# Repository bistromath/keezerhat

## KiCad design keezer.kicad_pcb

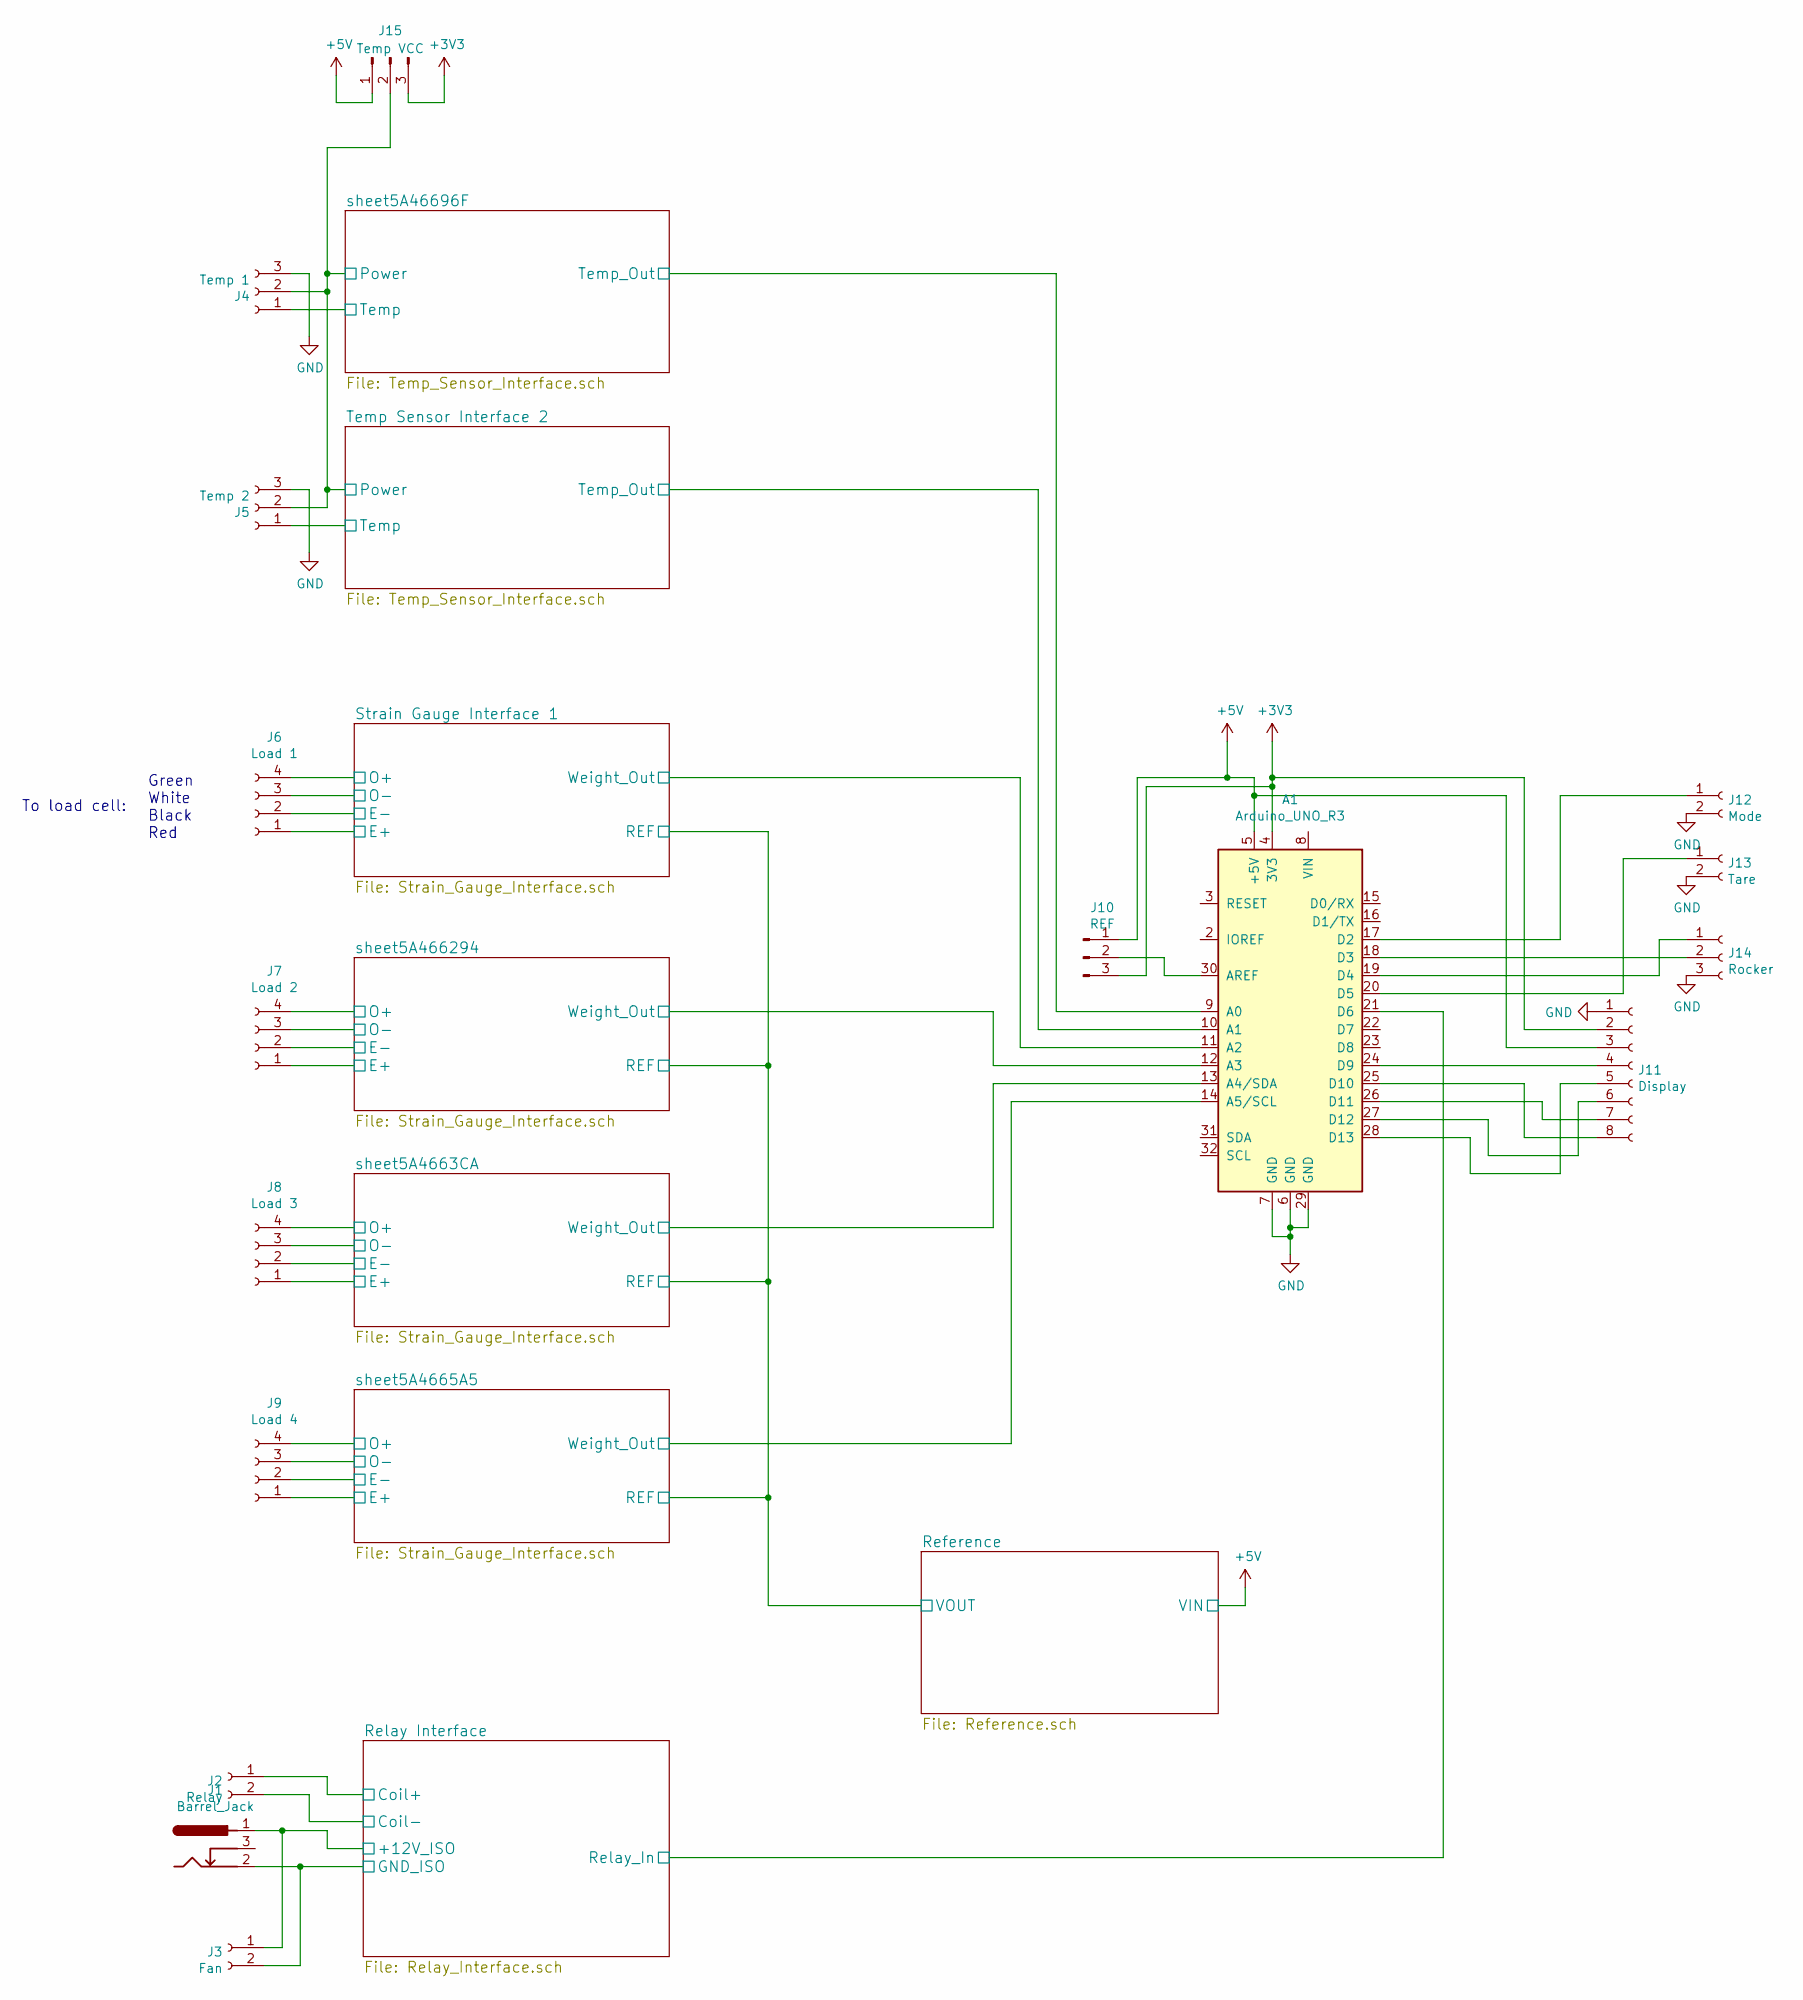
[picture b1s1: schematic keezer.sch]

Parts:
A1: Arduino_UNO_R3
J1: Barrel_Jack; Barrel_Jack_CUI_PJ-102AH
J2: Relay; Molex_NanoFit_1x02x2.50mm_Straight
J3: Fan; Molex_NanoFit_1x02x2.50mm_Straight
J4: Temp 1; Molex_NanoFit_1x03x2.50mm_Straight
J5: Temp 2; Molex_NanoFit_1x03x2.50mm_Straight
J6: Load 1; Molex_NanoFit_2x02x2.50mm_Straight
J7: Load 2; Molex_NanoFit_2x02x2.50mm_Straight
J8: Load 3; Molex_NanoFit_2x02x2.50mm_Straight
J9: Load 4; Molex_NanoFit_2x02x2.50mm_Straight
J10: REF; Pin_Header_Straight_1x03_Pitch2.54mm
J11: Display; Molex_NanoFit_2x04x2.50mm_Straight
J12: Mode; Molex_NanoFit_1x02x2.50mm_Straight
J13: Tare; Molex_NanoFit_1x02x2.50mm_Straight
J14: Rocker; Molex_NanoFit_1x03x2.50mm_Straight
J15: Temp VCC; Pin_Header_Straight_1x03_Pitch2.54mm

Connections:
+3V3: A1.4 (3V3), J10.3, J11.2, J15.3
+5V: A1.5 (+5V), J6.1, J7.1, J8.1, J9.1, J10.1, J11.3, J15.1; also elsewhere on the board
/Relay Interface/+12V_ISO: J1.1, J3.1; also elsewhere on the board
/Relay Interface/Coil+: J2.1; also elsewhere on the board
/Relay Interface/Coil-: J1.2, J2.2, J3.2; also elsewhere on the board
/Relay Interface/Relay_In: A1.21 (D6); also elsewhere on the board
/Strain Gauge Interface 1/O+: J6.4; also elsewhere on the board
/Strain Gauge Interface 1/O-: J6.3; also elsewhere on the board
/Strain Gauge Interface 1/Weight_Out: A1.11 (A2); also elsewhere on the board
/Temp Sensor Interface 2/Power: J4.2, J5.2, J15.2; also elsewhere on the board
/Temp Sensor Interface 2/Temp: J5.1; also elsewhere on the board
/Temp Sensor Interface 2/Temp_Out: A1.10 (A1); also elsewhere on the board
/sheet5A4663CA/O+: J8.4; also elsewhere on the board
/sheet5A4663CA/O-: J8.3; also elsewhere on the board
/sheet5A4663CA/Weight_Out: A1.13 (A4/SDA); also elsewhere on the board
/sheet5A4665A5/O+: J9.4; also elsewhere on the board
/sheet5A4665A5/O-: J9.3; also elsewhere on the board
/sheet5A4665A5/Weight_Out: A1.14 (A5/SCL); also elsewhere on the board
/sheet5A46696F/Temp: J4.1; also elsewhere on the board
/sheet5A46696F/Temp_Out: A1.9 (A0); also elsewhere on the board
/sheet5A466294/O+: J7.4; also elsewhere on the board
/sheet5A466294/O-: J7.3; also elsewhere on the board
/sheet5A466294/Weight_Out: A1.12 (A3); also elsewhere on the board
GND: A1.6 (GND), A1.7 (GND), A1.29 (GND), J4.3, J5.3, J6.2, J7.2, J8.2, J9.2, J11.1, J12.2, J13.2, J14.3; also elsewhere on the board
unnamed: A1.17 (D2), J12.1
unnamed: A1.18 (D3), J14.2
unnamed: A1.19 (D4), J14.1
unnamed: A1.20 (D5), J13.1
unnamed: A1.24 (D9), J11.4
unnamed: A1.25 (D10), J11.8
unnamed: A1.26 (D11), J11.7
unnamed: A1.27 (D12), J11.6
unnamed: A1.28 (D13), J11.5
unnamed: A1.30 (AREF), J10.2

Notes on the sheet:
Green White Black Red
To load cell:

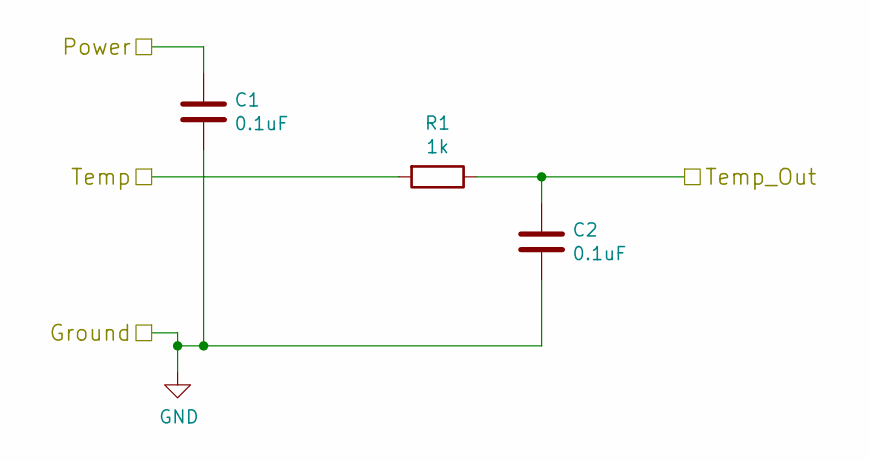
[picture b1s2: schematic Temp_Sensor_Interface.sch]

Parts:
C1, C2: 0.1uF; C_0805_HandSoldering
R1: 1k; R_0805_HandSoldering

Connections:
/Temp Sensor Interface 2/Power: C1.1; also elsewhere on the board
/Temp Sensor Interface 2/Temp: R1.2; also elsewhere on the board
/Temp Sensor Interface 2/Temp_Out: C2.1, R1.1; also elsewhere on the board
GND: C1.2, C2.2; also elsewhere on the board

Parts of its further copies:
C3, C4: 0.1uF; C_0805_HandSoldering
R4: 1k; R_0805_HandSoldering

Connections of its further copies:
/Temp Sensor Interface 2/Power: C3.1; also elsewhere on the board
/sheet5A46696F/Temp: R4.2; also elsewhere on the board
/sheet5A46696F/Temp_Out: C4.1, R4.1; also elsewhere on the board
GND: C3.2, C4.2; also elsewhere on the board

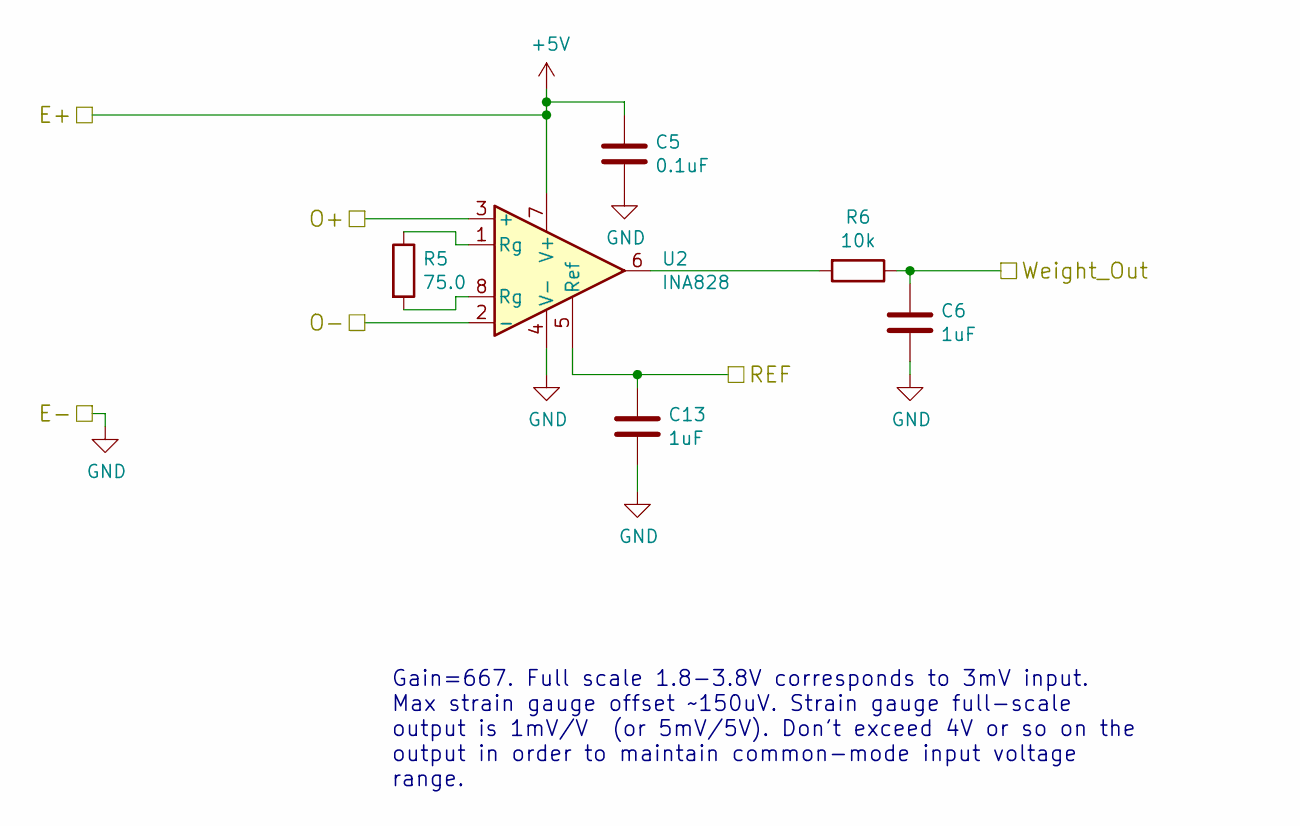
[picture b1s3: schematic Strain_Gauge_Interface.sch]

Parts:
C5: 0.1uF; C_0805_HandSoldering
C6, C16: 1uF; C_0805_HandSoldering
R5: 75.0; R_0805_HandSoldering
R6: 10k; R_0805_HandSoldering
U2: INA828; SOIC-8_3.9x4.9mm_Pitch1.27mm

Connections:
+5V: C5.1, U2.7 (V+); also elsewhere on the board
/Strain Gauge Interface 1/O+: U2.3 (+); also elsewhere on the board
/Strain Gauge Interface 1/O-: U2.2 (-); also elsewhere on the board
/Strain Gauge Interface 1/REF: C16.1, U2.5 (Ref); also elsewhere on the board
/Strain Gauge Interface 1/Weight_Out: C6.1, R6.1; also elsewhere on the board
GND: C5.2, C6.2, C16.2, U2.4 (V-); also elsewhere on the board
unnamed: R5.1, U2.1 (Rg)
unnamed: R5.2, U2.8 (Rg)
unnamed: R6.2, U2.6

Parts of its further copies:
C7, C9, C11: 0.1uF; C_0805_HandSoldering
C8, C10, C12, C13, C14, C15: 1uF; C_0805_HandSoldering
R7, R9, R11: 75.0; R_0805_HandSoldering
R8, R10, R12: 10k; R_0805_HandSoldering
U3, U4, U5: INA828; SOIC-8_3.9x4.9mm_Pitch1.27mm

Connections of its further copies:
+5V: C7.1, C9.1, C11.1, U3.7 (V+), U4.7 (V+), U5.7 (V+); also elsewhere on the board
/Strain Gauge Interface 1/REF: C13.1, C14.1, C15.1, U3.5 (Ref), U4.5 (Ref), U5.5 (Ref); also elsewhere on the board
/sheet5A4663CA/O+: U4.3 (+); also elsewhere on the board
/sheet5A4663CA/O-: U4.2 (-); also elsewhere on the board
/sheet5A4663CA/Weight_Out: C10.1, R10.1; also elsewhere on the board
/sheet5A4665A5/O+: U5.3 (+); also elsewhere on the board
/sheet5A4665A5/O-: U5.2 (-); also elsewhere on the board
/sheet5A4665A5/Weight_Out: C12.1, R12.1; also elsewhere on the board
/sheet5A466294/O+: U3.3 (+); also elsewhere on the board
/sheet5A466294/O-: U3.2 (-); also elsewhere on the board
/sheet5A466294/Weight_Out: C8.1, R8.1; also elsewhere on the board
GND: C7.2, C8.2, C9.2, C10.2, C11.2, C12.2, C13.2, C14.2, C15.2, U3.4 (V-), U4.4 (V-), U5.4 (V-); also elsewhere on the board
unnamed: R7.1, U3.1 (Rg)
unnamed: R7.2, U3.8 (Rg)
unnamed: R8.2, U3.6
unnamed: R9.1, U4.1 (Rg)
unnamed: R9.2, U4.8 (Rg)
unnamed: R10.2, U4.6
unnamed: R11.1, U5.1 (Rg)
unnamed: R11.2, U5.8 (Rg)
unnamed: R12.2, U5.6

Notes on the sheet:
Gain=667. Full scale 1.8-3.8V corresponds to 3mV input. Max strain gauge offset ~~150uV. Strain gauge full-scale output is 1mV/V (or 5mV/5V). Don't exceed 4V or so on the output in order to maintain common-mode input voltage range.

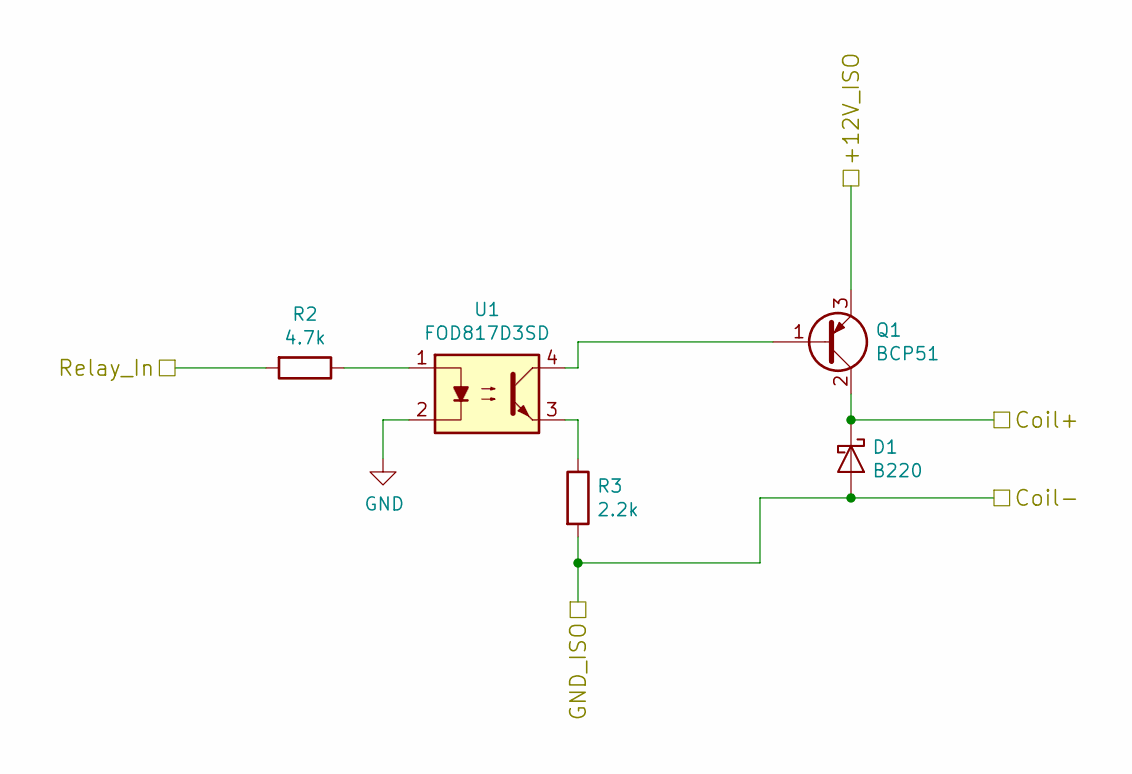
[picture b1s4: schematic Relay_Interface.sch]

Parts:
D1: B220; D_SMB_Handsoldering
Q1: BCP51; SOT-223-3_TabPin2
R2: 4.7k; R_0805_HandSoldering
R3: 2.2k; R_0805_HandSoldering
U1: FOD817D3SD; SO-4_4.4x3.6mm_Pitch2.54mm

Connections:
/Relay Interface/+12V_ISO: Q1.3 (E); also elsewhere on the board
/Relay Interface/Coil+: D1.1 (K), Q1.2 (C); also elsewhere on the board
/Relay Interface/Coil-: D1.2 (A), R3.2; also elsewhere on the board
/Relay Interface/Relay_In: R2.2; also elsewhere on the board
GND: U1.2; also elsewhere on the board
unnamed: Q1.1 (B), U1.4
unnamed: R2.1, U1.1
unnamed: R3.1, U1.3

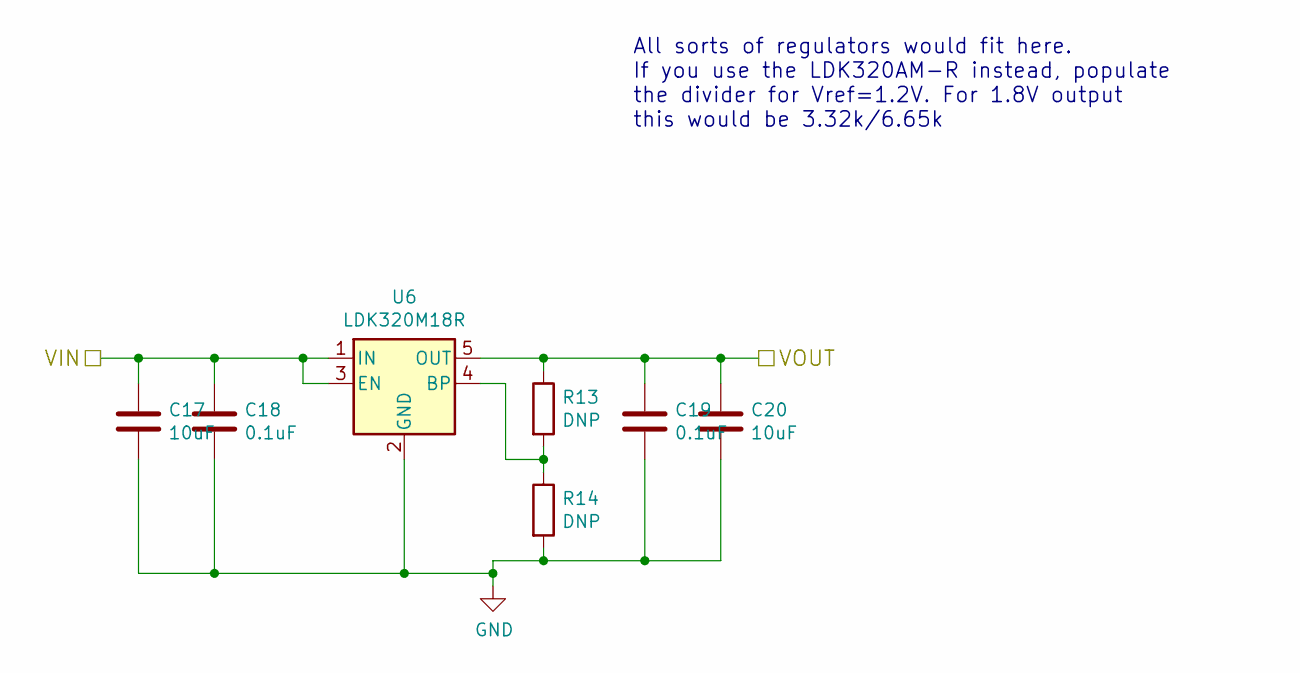
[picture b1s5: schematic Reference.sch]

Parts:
C17, C20: 10uF; C_0805_HandSoldering
C18, C19: 0.1uF; C_0805_HandSoldering
R13, R14: DNP; R_0805_HandSoldering
U6: LDK320M18R; SOT-23-5_HandSoldering

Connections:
+5V: C17.1, C18.1, U6.1 (IN), U6.3 (EN); also elsewhere on the board
/Strain Gauge Interface 1/REF: C19.1, C20.1, R13.1, U6.5 (OUT); also elsewhere on the board
GND: C17.2, C18.2, C19.2, C20.2, R14.2, U6.2 (GND); also elsewhere on the board
unnamed: R13.2, R14.1, U6.4 (BP)

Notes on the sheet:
All sorts of regulators would fit here. If you use the LDK320AM-R instead, populate the divider for Vref=1.2V. For 1.8V output this would be 3.32k/6.65k

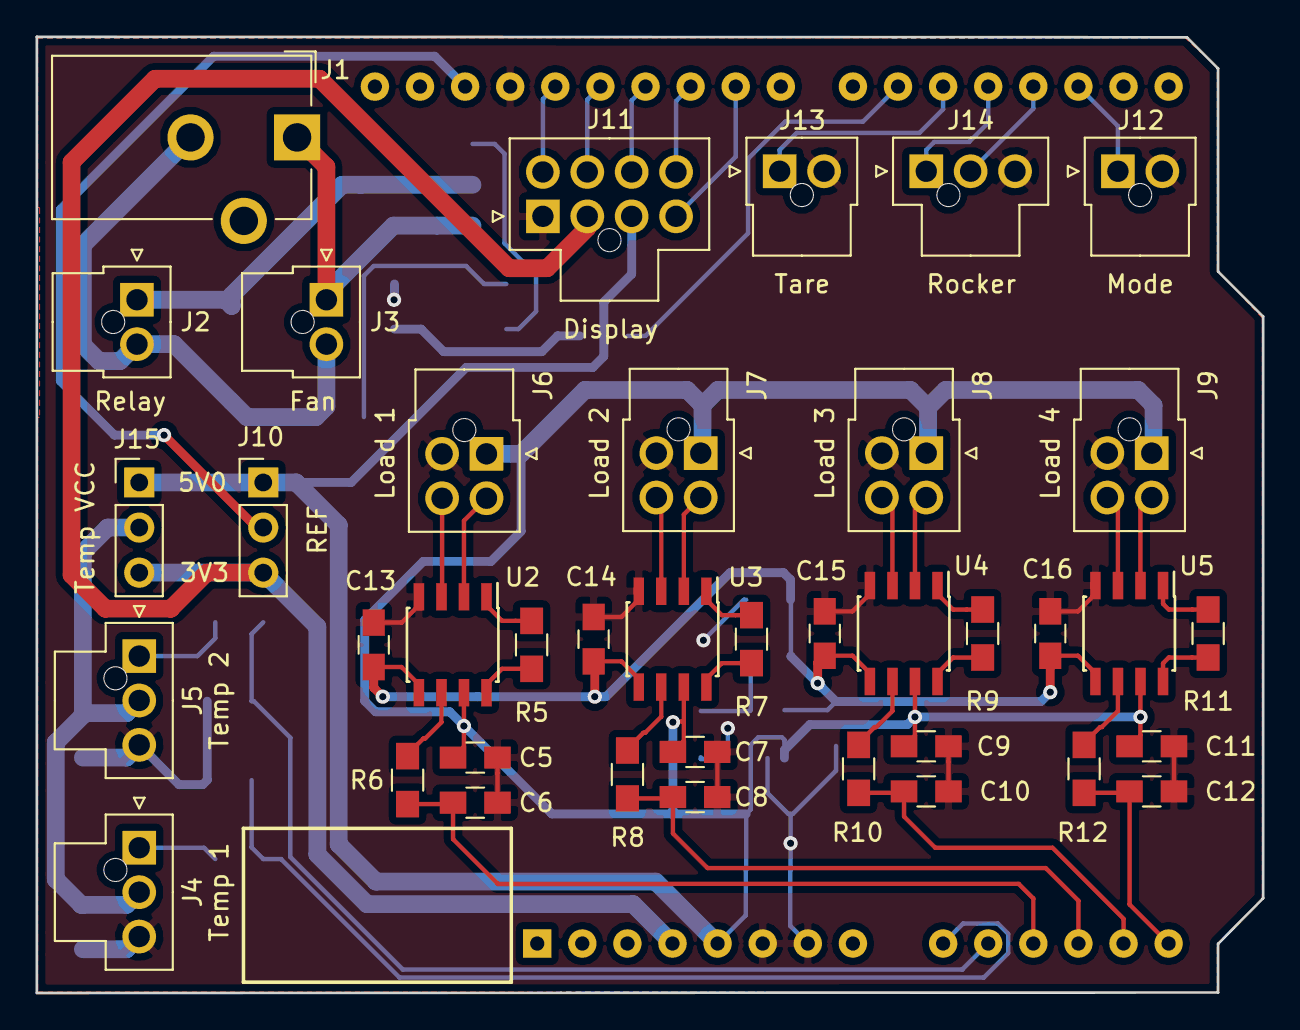
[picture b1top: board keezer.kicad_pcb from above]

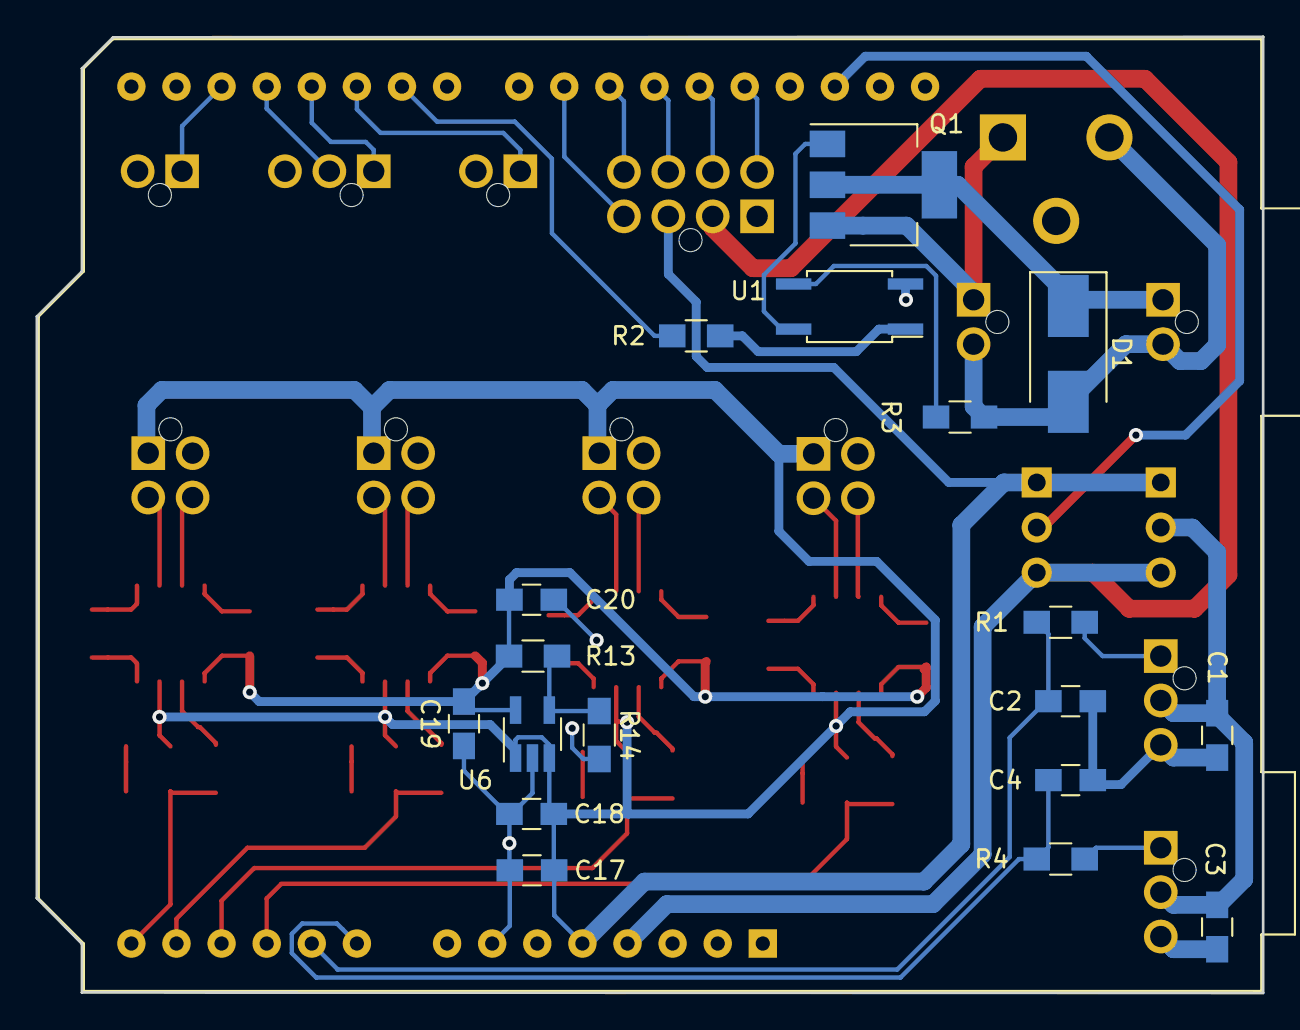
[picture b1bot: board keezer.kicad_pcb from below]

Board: 2 copper layers, 69.1 x 53.8 mm, 58 parts (19 on the bottom side), 51 nets.

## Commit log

2017-12-30 Initial commit.
2017-12-31 Pretty much ready to go. Should verify barrel jack first. Needs a logo.
2018-01-01 Cosmetic changes mostly.
2018-01-05 Logo. Finally.
